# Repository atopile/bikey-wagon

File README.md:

<div align="center">

# bikey_wagon

<br/>

A controller for the bikey wagon project

</div>

## About

Type here your detailed project description.

This project is build with the open-source EDA [faebryk](https://github.com/faebryk/faebryk).

## Working with the source files

See [here](./docs/development.md) for the instructions on how to install and edit this project.

## Building

If you want to physicaly build this project, you can find the build instructions [here](./docs/build_instructions.md).

## Contributing

If you want to share your alterations, improvements, or add bugfixes to this project, please take a look at the [contributing guidelines](./docs/CONTRIBUTING.md).

## Community Support

Community support is provided via Discord; see the Resources below for details.

### Resources

- Source Code: [Github](https://github.com/atopile/bikey-wagon-faebryk)
- Chat: Real-time chat happens in faebryk's Discord Server (show-off). Use this Discord [Invite](https://discord.gg/95jYuPmnUW) to register
- Issues: [Issues](https://github.com/atopile/bikey-wagon-faebryk/issues)

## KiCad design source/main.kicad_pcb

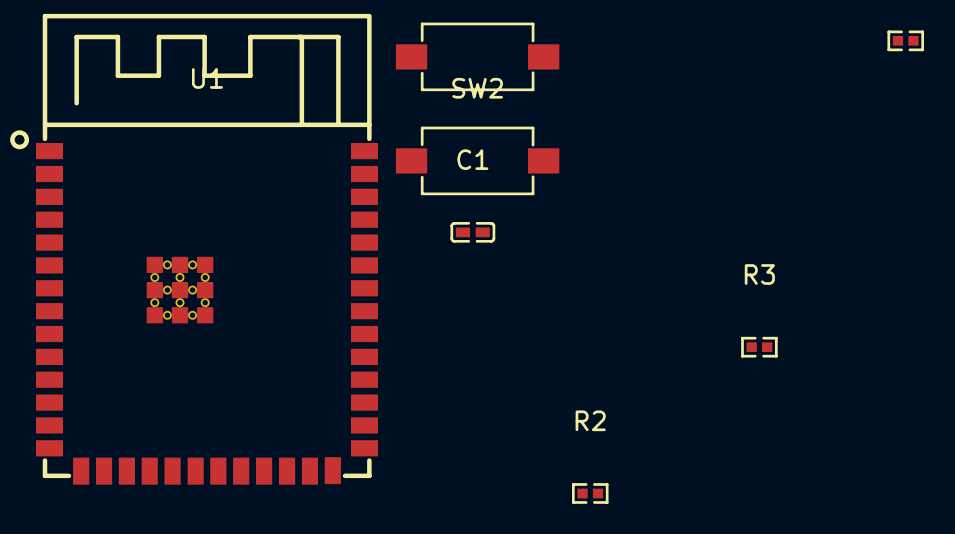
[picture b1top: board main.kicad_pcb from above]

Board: 2 copper layers, 7 parts (0 on the bottom side), 4 nets, no tracks yet.

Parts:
C1: 20pF ±5% 50V C0G; C0402
R1, R2: 7.5kΩ ±1% 62.5mW; R0402
R3: 100Ω; R0402
SW1, SW2: _Switch; SW-SMD_L6.0-W3.5-LS8.0
U1: ESP32_S3_WROOM_1_N16R8; WIRELM-SMD_ESP32-S3-WROOM-1

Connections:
C1-1-R1-2-R2-2-U1-2: C1.1, R1.2, R2.2, U1.2
C1-2-SW1-2-SW2-2-U1-1-U1-40-U1-41: C1.2, SW1.2, SW2.2, U1.1, U1.40, U1.41
R1-1-SW1-1: R1.1, SW1.1
R2-1-SW2-1: R2.1, SW2.1

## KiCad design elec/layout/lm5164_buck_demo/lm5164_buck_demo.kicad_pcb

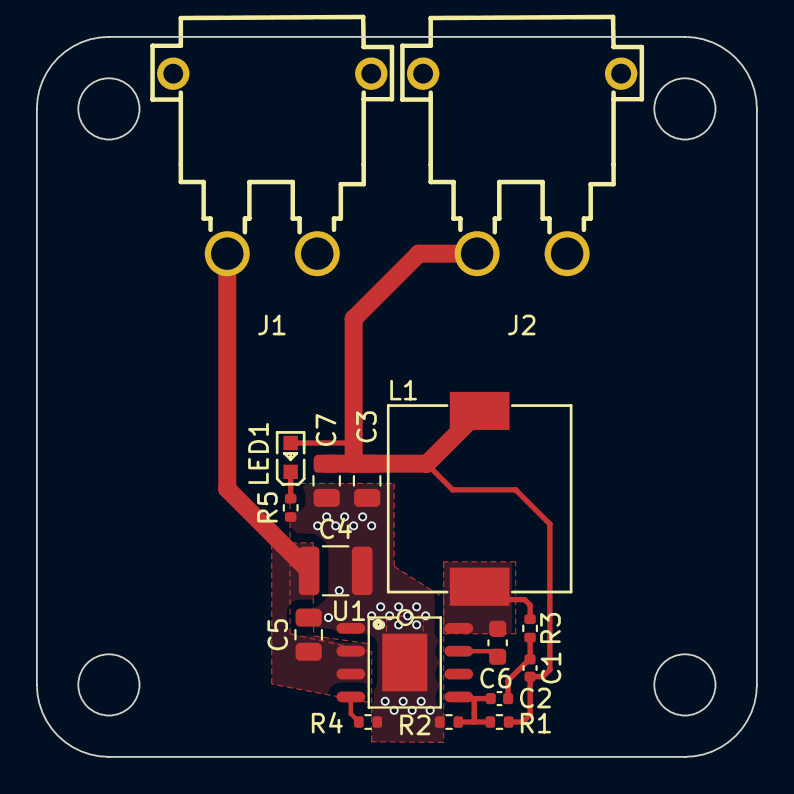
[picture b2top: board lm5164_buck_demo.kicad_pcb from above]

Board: 2 copper layers, 40.0 x 40.0 mm, 17 parts (0 on the bottom side), 9 nets.

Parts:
C1: 50V 4.7nF X7R ±10% 0402 Multilayer Ceramic Capaci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; C0402
C2: 50V 47pF C0G ±5% 0402 Multilayer Ceramic Capacito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; C0402
C3, C7: 22uF +/- 20%; C0805
C4: 4.7uF +/- 10%; C1210
C5: 220nF +/- 10%; C0805
C6: 50V 100nF X7R ±10% 0603 Multilayer Ceramic Capaci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; C0603
J1, J2: CONN-TH_XT30PW-M
L1: 68uH +/- 20%; IND-SMD_L10.2-W10.0
LED1: LED0603-RD
R1, R3: 62.5mW Thick Film Resistors 50V ±100ppm/℃ ±1% 374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; R0402
R2: 62.5mW Thick Film Resistors 50V ±100ppm/℃ ±1% 51k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; R0402
R4: 62.5mW Thick Film Resistors ±100ppm/℃ ±1% 69.8kΩ 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; R0402
R5: 62.5mW Thick Film Resistors 50V ±100ppm/℃ ±1% 5.1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; R0402
U1: SO-8_L4.9-W3.9-P1.27-LS6.0-BL-EP

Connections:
bst: C6.2, U1.7
buck-vcc: C4.1, C5.1, J1.2, U1.2, U1.3
buck-vcc-1: C1.1, C3.1, C7.1, J2.2, L1.2, LED1.2, R1.1
buck.Ra-vcc: C1.2, C2.1, R3.2
cathode: LED1.1, R5.1
gnd: C3.2, C4.2, C5.2, C7.2, J1.1, J2.1, R2.2, R4.2, R5.2, U1.1, U1.9
out: C2.2, R1.2, R2.1, U1.5
ron: R4.1, U1.4
sw: C6.1, L1.1, R3.1, U1.8

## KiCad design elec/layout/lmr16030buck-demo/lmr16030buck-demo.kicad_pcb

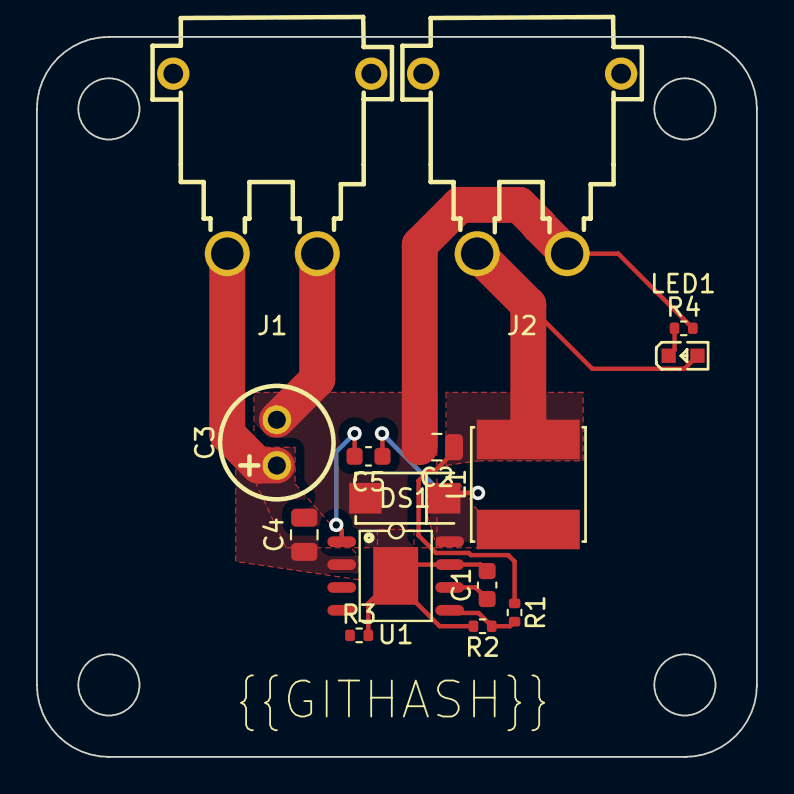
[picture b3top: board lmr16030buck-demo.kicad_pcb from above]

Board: 2 copper layers, 40.0 x 40.0 mm, 15 parts (0 on the bottom side), 9 nets.

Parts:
C1: 50V 10nF X7R ±10% 0603 Multilayer Ceramic Capacit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; C0603
C2: 22uF +/- 20%; C0805
C3: 4.7uF to 10uF; CAP-TH_BD6.3-P2.50-D1.0-FD
C4: 100nF +/- 21%; C0805
C5: 50V 100nF X7R ±10% 0603 Multilayer Ceramic Capaci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; C0603
DS1: SMA_L4.4-W2.6-LS5.0-RD
J1, J2: CONN-TH_XT30PW-M
L1: 8.2uH +/- 20%; IND-SMD_L6.2-W6.2
LED1: LED0603-RD
R1: 62.5mW Thick Film Resistors 50V ±100ppm/℃ ±1% 13.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; R0402
R2: 62.5mW Thick Film Resistors 50V ±100ppm/℃ ±1% 3.9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; R0402
R3: 62.5mW Thick Film Resistors 50V ±100ppm/℃ ±1% 36.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; R0402
R4: 100mW Thick Film Resistors ±100ppm/℃ ±1% 1.07kΩ 0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; R0402
U1: SO-8_L4.9-W3.9-P1.27-LS6.0-BL-EP

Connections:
boot: C5.2, U1.1
buck-vcc: C3.1, C4.1, J1.2, U1.2
buck-vcc-1: C2.1, J2.2, L1.2, LED1.2, R1.1
cathode: LED1.1, R4.1
gnd: C1.2, C2.2, C3.2, C4.2, DS1.2, J1.1, J2.1, R2.2, R3.2, R4.2, U1.7, U1.9
out: R1.2, R2.1, U1.5
rt_slash_sync: R3.1, U1.4
ss: C1.1, U1.6
sw: C5.1, DS1.1, L1.1, U1.8

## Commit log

2024-05-09 Configure project
2024-05-10 Not building yet, but a good demo of how a regulator can be designed
2024-05-10 Rename project
2024-05-11 Add remainder of configuration for step-down converter
2024-05-15 Add demo of LMR16030
2024-05-15 Add implementation of a 3.3V supply
2024-05-15 Exclude broken build targets
2024-05-24 Add additional constraints rather than component selections
2024-05-24 Remove generics
2024-05-24 Top-level systems equations
2024-05-25 Fix .vcc in Pair
2024-05-27 Configure power-stages and 10v supply
2024-05-28 checkpoint
2024-05-28 Add content to README
2024-05-28 Add image to README
2024-07-19 Bring current feedback gains into range
2024-07-22 add new higher voltage, lower cost regulator
2024-07-22 add footprint;
2024-07-25 fix nonexistant servo-drive reference
2024-07-26 Hopefully this universally builds now
2024-07-27 picked new inductor, buils
2024-07-28 layout lm5164 demo, generate outputs
2024-07-29 add to bikey-wagon.ato, add feedback ripple circuit
2024-07-29 use a couple more basic jlc parts
2024-07-29 attempt to add assertions for ripple generator. not working, so commented out
2024-08-01 fixed feedback ripple generation assertions
2024-08-01 fix lm5164 import
2024-08-01 branch for Matt
2024-08-13 Proof of life
2024-08-13 Add ESP32 module
2024-08-15 Generally working ESP32-S3
2024-08-15 KiCAD resources reloaded
2024-08-15 Connect up references
2024-08-16 Add DRV8300 power-stage
2024-08-30 Upgrade ESP32-S3 to new holders
2024-09-03 Upgrade app for new holders
2024-09-04 FabLL update
2024-09-04 It builds again

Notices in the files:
README.md:
License: MIT
